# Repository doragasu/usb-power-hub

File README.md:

# usb-power-hub
Just a plain PCB distributing power from a DC barrel jack to 5 USB A female connectors.

PCB is designed to fit inside a Hammond RL6115 enclosure.

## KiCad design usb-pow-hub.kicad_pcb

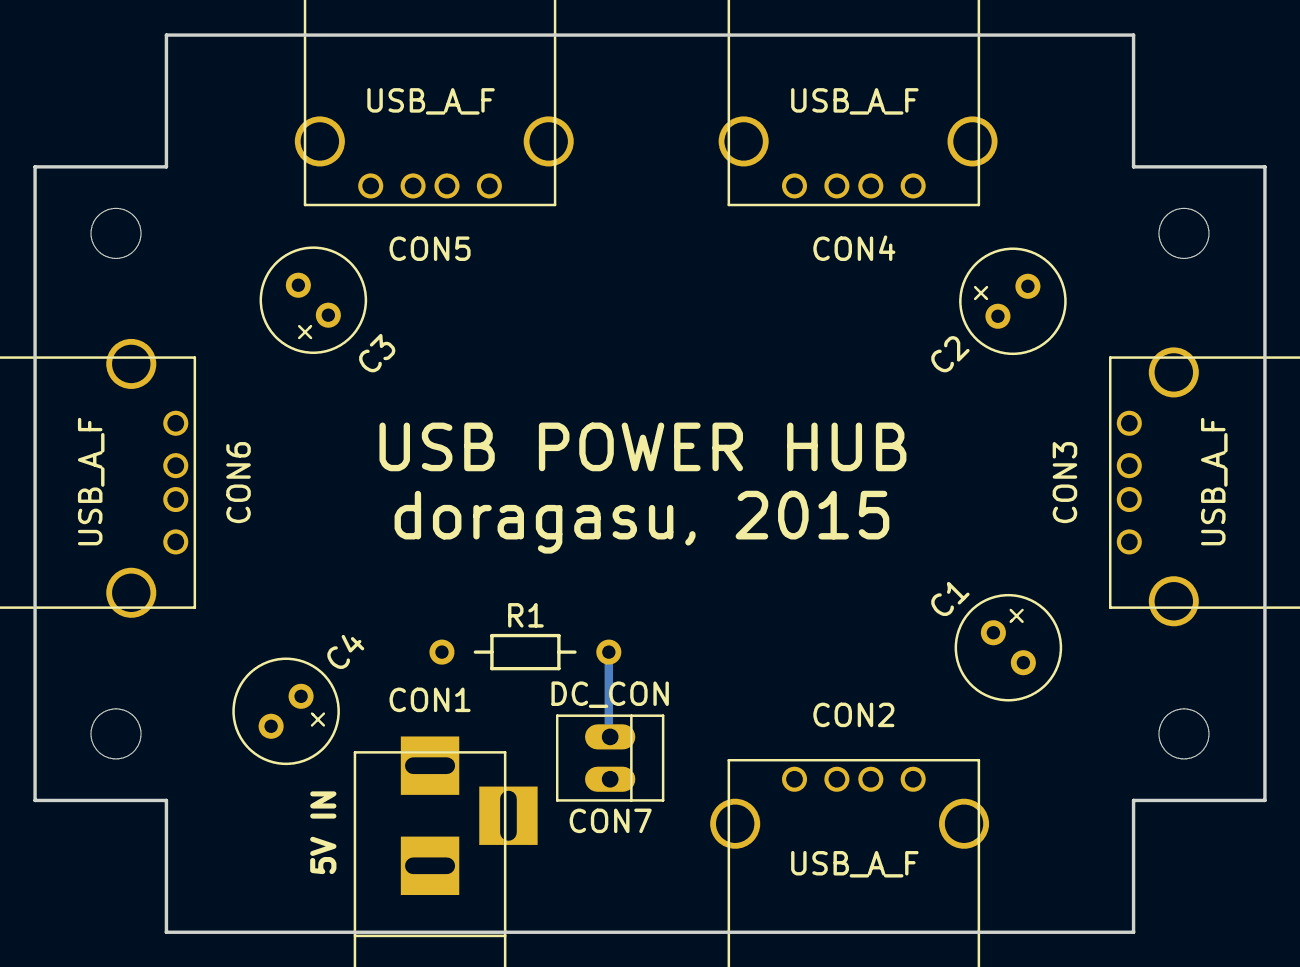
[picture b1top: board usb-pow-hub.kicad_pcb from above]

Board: 2 copper layers, 73.7 x 53.8 mm, 16 parts (0 on the bottom side), 3 nets.

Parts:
C1, C2, C3, C4: 100u; Elko_vert_11.2x6.3mm_RM2.5_CopperClear
CON1: BARREL_JACK
CON2, CON3, CON4, CON5, CON6: USB_A_F; USB_A
CON7: DC_CON; PINHEAD1-2
MountingHole_3mm, MountingHole_3mm#2, MountingHole_3mm#3, MountingHole_3mm#4: VAL**; MountingHole_3mm
R1: 330; Resistor_Horizontal_RM10mm

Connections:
GND: C1.2, C2.2, C3.2, C4.2, CON1.2, CON1.3, CON2.4, CON2.5, CON2.6, CON3.4, CON3.5, CON3.6, CON4.4, CON4.5, CON4.6, CON5.4, CON5.5, CON5.6, CON6.4, CON6.5, CON6.6, CON7.2
unnamed: CON7.1, R1.2
VCC: C1.1, C2.1, C3.1, C4.1, CON1.1, CON2.1, CON3.1, CON4.1, CON5.1, CON6.1, R1.1

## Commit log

2015-05-16 Added project files.
